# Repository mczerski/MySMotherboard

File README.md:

# MySMotherboard
## Motherboard for MySensors nodes

This is a motherboard for creating MySensors nodes based on the atmega328p MCU. It is meant to be combined with a MySX daughter board to create fully functional MySensors node. It is primarly for battery powered nodes but can be also used as a gateway or ac powered node (ac power supply is not part of this project). It features multiple powering options and supports RS485 or RFM69 RF communication options. The size of the board is just a little bigger than a cr123a battery holder.

## Features:

1. atmega328p MCU
2. Multiple power source options:
  * CR123A battery or 16340 rechargable li-ion battery
  * CR2032 battery
  * JST-PH2 connector for rechargable li-ion battery
  * 24V on the 2.54mm screw terminal
  * VRAW from MySX connector
3. Multiple voltage regulator options:
  * MCP1640C boost converter with bypass option
  * TPS782 LDO linear regulator
  * AP63205WU buck converter
  * no voltage regulation - direct voltage from battery
4. Input voltage reverse polarity protection
5. Overvoltage protection for RS485 data lines
6. Battery voltage divider to monitor battery voltage
7. ATSHA204A supported
8. AT25DF512C flash suppoerted
9. RFM69 RF SMD module
10. RF module interrupt D2 pin can be disconnected if not used
11. SP3485 for RS485 communication
12. reset button
13. user button
14. user led
15. external oscillator for atmega

## HOW TO

### Minimum required parts to solder are:

1. MCU related parts:
C5, C6, C7, C10, IC5, R7
2. Radio module related parts:
C1, R1, RFM69W, antenna to ANT pad and R12 (R12 is just a 0Ohm jumper required to connect RFM69 interrupt with D2 pin)
3. RS485 interface related parts:
U8
3. MySX connector:
X2

This is bare minimum that is required to start with this board. In this configuration the board can be powered from the MySX connector VCC pin with voltage between 1.9V - 3.6V.

### Optional parts to solder are:

1. MCU related parts:
 * for user led - R8, D1
 * for reset button - RST
 * for user button connected to D2 pin - BTN
 * for I2C pull-up resistors - R9, R10
 * for external oscillator - C8, C9, Q2
2. External flash related parts:
R2, IC2
WARNING: flash chips consumes a lot of uA of current so it is not suited for battery powered nodes.
3. ATSHA204A related parts:
IC3
ATSHA204A requires at least 2.0V power supply
4. RS485 related parst (overvoltage protection on data pins):
F1, F2, D2, D3

### Powering options

The powering option is choosed in two steps. First is to select the voltage source, and second is to choose the voltage conversion type. Between the voltage source and the voltage converter ther is the reverse polarity protection mosfet Q1 which is required for all options and voltage divider for battery voltage monitoring which is not required.

Voltage source options are:
1. CR123A battery or 16340 rechargable li-ion battery. To select this option just solder CR123A battery holder.
2. CR2032 battery. To chosse this option just solder CR2032 battery holder.
3. JST-PH2 connector. To choose this option just solder the X1 connector.
4. 24V input on 2.54mm screw terminal
5. VRAW from MySX connector. To choose this option the J2 jumper must be shorted.

Reverse polarity battery protection:
Q1

Voltage divider for battery voltage monitoring:
R5, R6, C4

Voltage convertion options are:
1. MCP1640C boost converter
R3, R4, R11, C2, C3, L1, IC4, J1 jumper should connect VBOOST with VCC.
The MCP1640C boost converter can be put into bypass mode so it just passes the input voltage. It is controller by the A2 pin and the bypass mode is the default. The purpose of this functionality is to be able to run the MCU directly from the battery and to boost the voltage only for the moment required to make measurements with sensors that require higher voltages.
2. TPS782 LDO linear regulator
C13, C14, IC1. J1 jumper should connect VREG with VCC. The C12 should be replaced by the 0Ohm resistor. The C12 capacitor was designed for the APE8865 LDo which consumes much more current that TPS782.
3. AP63205WU buck converter
C1, C6, C11, U7, Q2 (for high voltage reverse polarity protection)
4. No voltage regulation
There is actually no direct way to shoose this option, but it can be done by shorting pins number 5 and 6 of the IC4 and J1 jumper should connect VBOOST with VCC.

### Powering examples.

1. Very low power temperature and humidity sensor based on the BME280 sensor.
This node uses the "No voltage conversion" option because the BME280 sensor can work with voltages as low as 1.2V. So the node may be powered just by 3V coin-cell battery. This type of node uses just CR2032 battery holder.

2. Very low power node with DS18B20 temperature sensors that require minimum 3V power supply.
This type of node uses MCP1640C boost converter to boost battery voltage for the measurement period. Use CR2032 battery holder and MCP1640C boost converter option. In the software controll properly the A2 pin to turn on/off boost conversion.

3. Motion sensor node.
Motion sensor such as AS312 consumes quite a lot of power and needs voltage between 2.7V and 3.3V. Powering it directly with 3V battery is not good, so we could use the boost converter. But boost converter makes to much noise for AS312 to work properly. The AS312 works the best with 3V LDO, so the power source should have higher voltage. The best options is to use 3.7V 16340 rechargable li-ion battery which fits into CR123A battery holder. Use TPS782 LDO option to power the MCU and RF module and short the J2 jumper to power the VRAW pin directly with 3.7V battery. Then the motion sensor daugher board should power the AS312 sensor with another LDO from the VRAW pin.

4. RS485 node.
RS485 node uses 24V input on the 2.54mm screw terminal which delivers power and RS485 communication to the board. It also utilises high voltage reverse polarity protection and overvoltage protection for data pins so any wiring mistakes will not cause damage to the board. Onboard AP63205WU buck converter provides 5V input voltage for the board which can be used directly or can be fed to the 3V LDO regulator. By soldering JP1 jumper 5V power can be connected to VRAW on the MySX connector.

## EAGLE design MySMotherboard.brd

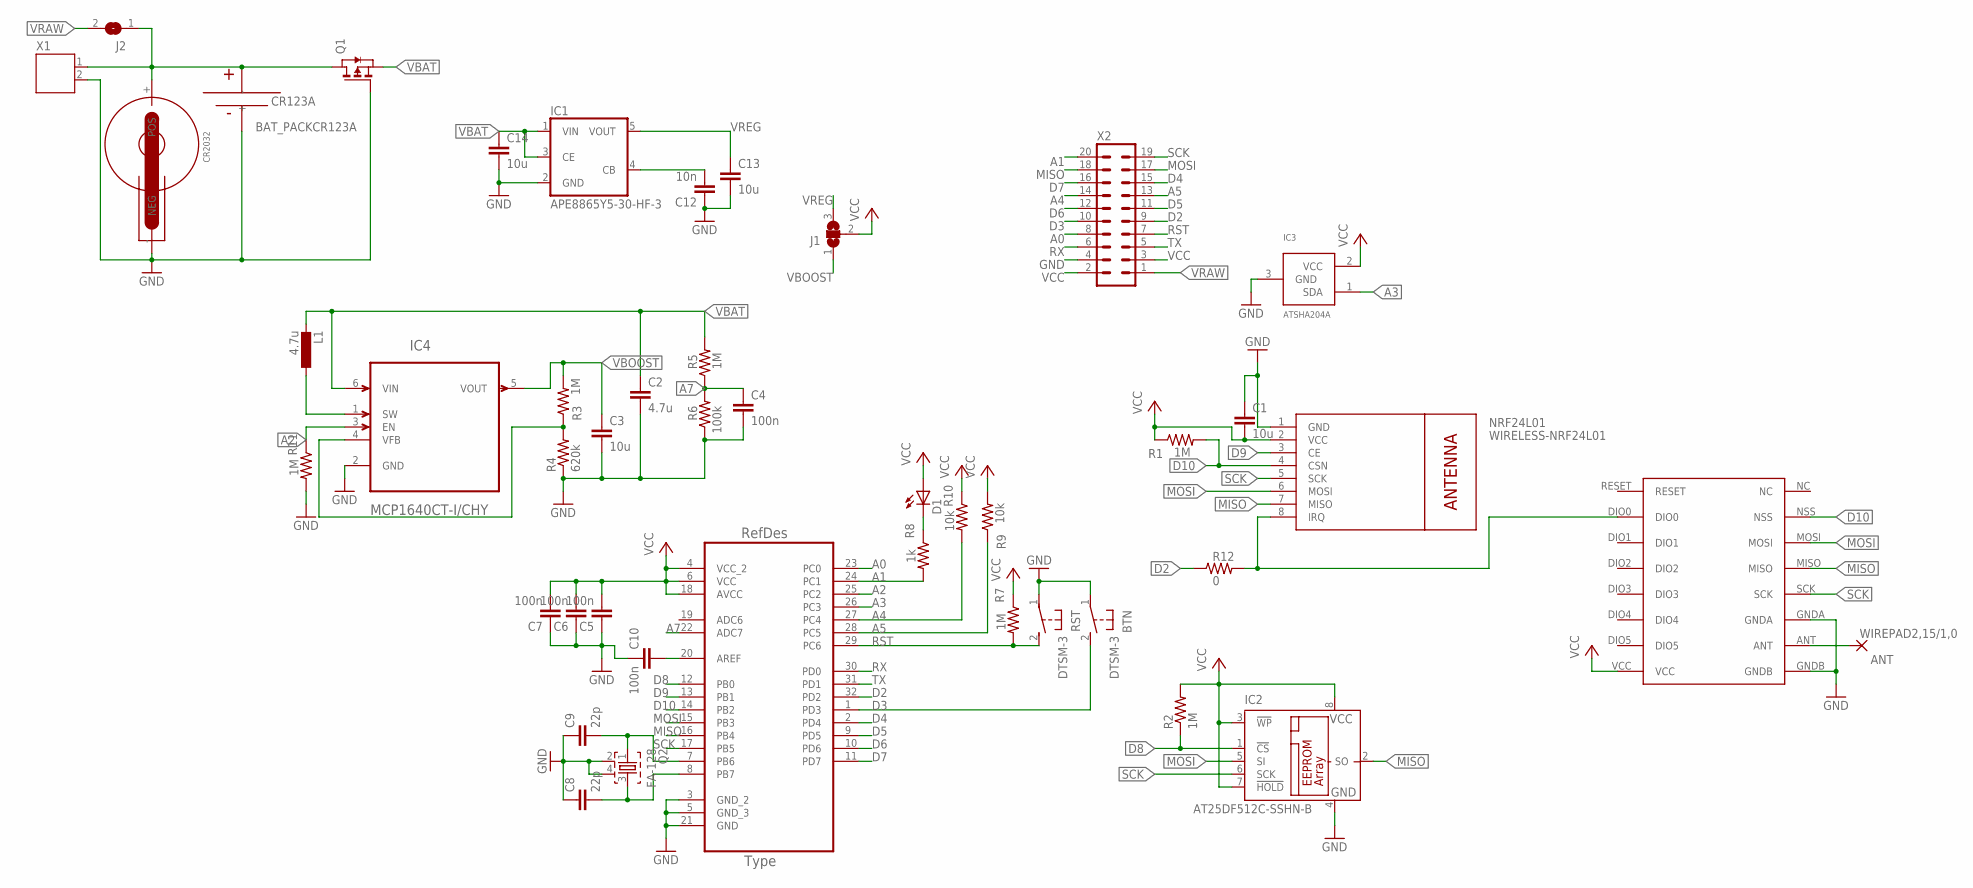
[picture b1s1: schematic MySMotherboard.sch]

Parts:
ANT: WIREPAD2,15/1,0; 2,15/1,0
BTN: DTSM-3
C1, C3, C13, C14: 10u; C0603K
C2: 4.7u; C0603K
C4, C5, C6, C7, C10: 100n; C0402
C8, C9: 22p; 0402-CAP
C12: 10n; C0402
CR123A: BAT_PACKCR123A; BH123A
CR2032: WA-BCPH_SMT_79527141; 79527141
D1: LEDCHIP-LED0805; CHIP-LED0805
IC1: APE8865Y5-30-HF-3; SOT25
IC2: AT25DF512C-SSHN-B; SO-08
IC3: ATSHA204A; SOT23
IC4: MCP1640CT-I/CHY; SOT95P270X145-6N
IC5: ATMEGA328P-AU; QFP80P900X900X120-32N
J1: SJ2W; SJ_2
J2: SJ
L1: 4.7u; L3225P
NRF24L01: WIRELESS-NRF24L01
Q1: PMOSSOT23; SOT-23
Q2: FA-128
R1, R2, R3, R7, R11: 1M; R0603
R4: 620k; R0603
R5: 1M; 0603-RES
R6: 100k; 0603-RES
R8: 1k; R0603
R9, R10: 10k; R0603
R12: 0; 0603-RES
RFM69W: RFM69HW; RFM
RST: DTSM-3
X1: JST-PH2
X2: MA10-2

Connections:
A0: IC5.23 (PC0), X2.8
A1: IC5.24 (PC1), R8.2, X2.20
A2: IC4.3 (EN), IC5.25 (PC2), R11.1
A3: IC3.1 (SDA), IC5.26 (PC3)
A4: IC5.27 (PC4), R10.2, X2.14
A5: IC5.28 (PC5), R9.1, X2.13
A7: C4.1, IC5.22 (ADC7), R5.1, R6.2
D2: IC5.32 (PD2), R12.1, X2.9
D3: BTN.2, IC5.1 (PD3), X2.10
D4: IC5.2 (PD4), X2.15
D5: IC5.9 (PD5), X2.11
D6: IC5.10 (PD6), X2.12
D7: IC5.11 (PD7), X2.16
D8: IC2.1 (!CS), IC5.12 (PB0), R2.1
D9: IC5.13 (PB1), NRF24L01.3 (CE)
D10: IC5.14 (PB2), NRF24L01.4 (CSN), R1.2, RFM69W.NSS
GND: BTN.1, C1.1, C2.2, C3.2, C4.2, C5.1, C6.1, C7.1, C8.1, C9.1, C10.2, C12.1, C13.2, C14.2, CR123A.-, CR2032.- (NEG), IC1.2 (GND), IC2.4 (GND), IC3.3 (GND), IC4.2 (GND), IC5.3 (GND_2), IC5.5 (GND_3), IC5.21 (GND), NRF24L01.1 (GND), Q1.3 (G), Q2.2, Q2.4, R4.1, R6.1, R11.2, RFM69W.GNDA, RFM69W.GNDB, RST.1, X1.2, X2.4
MISO: IC2.2 (SO), IC5.16 (PB4), NRF24L01.7 (MISO), RFM69W.MISO, X2.18
MOSI: IC2.5 (SI), IC5.15 (PB3), NRF24L01.6 (MOSI), RFM69W.MOSI, X2.17
unnamed: IC4.4 (VFB), R3.1, R4.2
unnamed: C8.2, IC5.8 (PB7), Q2.3
unnamed: C10.1, IC5.20 (AREF)
unnamed: IC4.1 (SW), L1.1
unnamed: ANT.1, RFM69W.ANT
unnamed: C9.2, IC5.7 (PB6), Q2.1
unnamed: CR123A.+, CR2032.+ (POS), J2.1, Q1.1 (D), X1.1
unnamed: C12.2, IC1.4 (CB)
unnamed: NRF24L01.8 (IRQ), R12.2, RFM69W.DIO0
unnamed: D1.C, R8.1
RST: IC5.29 (PC6), R7.2, RST.2, X2.7
RX: IC5.30 (PD0), X2.6
SCK: IC2.6 (SCK), IC5.17 (PB5), NRF24L01.5 (SCK), RFM69W.SCK, X2.19
TX: IC5.31 (PD1), X2.5
VBAT: C2.1, C14.1, IC1.1 (VIN), IC1.3 (CE), IC4.6 (VIN), L1.2, Q1.2 (S), R5.2
VBOOST: C3.1, IC4.5 (VOUT), J1.1, R3.2
VCC: C1.2, C5.2, C6.2, C7.2, D1.A, IC2.3 (!WP), IC2.7 (!HOLD), IC2.8 (VCC), IC3.2 (VCC), IC5.4 (VCC_2), IC5.6 (VCC), IC5.18 (AVCC), J1.2, NRF24L01.2 (VCC), R1.1, R2.2, R7.1, R9.2, R10.1, RFM69W.VCC, X2.2, X2.3
VRAW: J2.2, X2.1
VREG: C13.1, IC1.5 (VOUT), J1.3

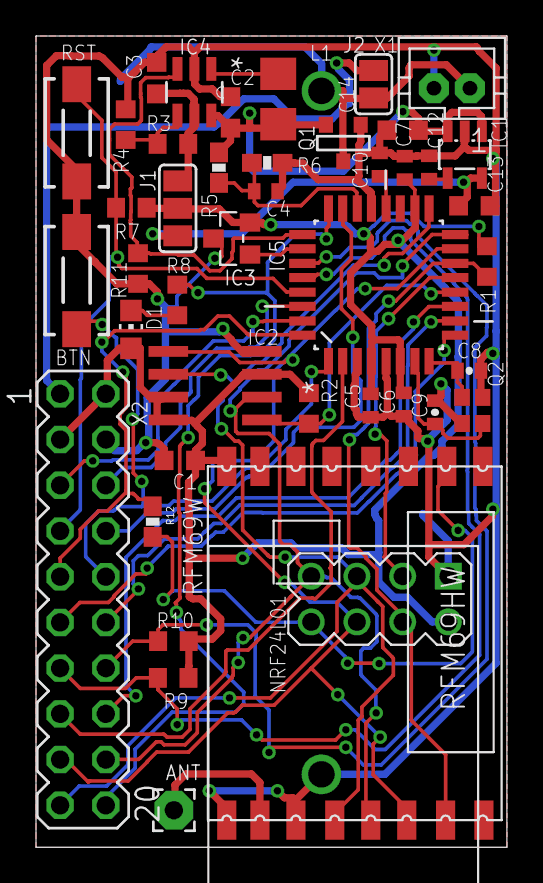
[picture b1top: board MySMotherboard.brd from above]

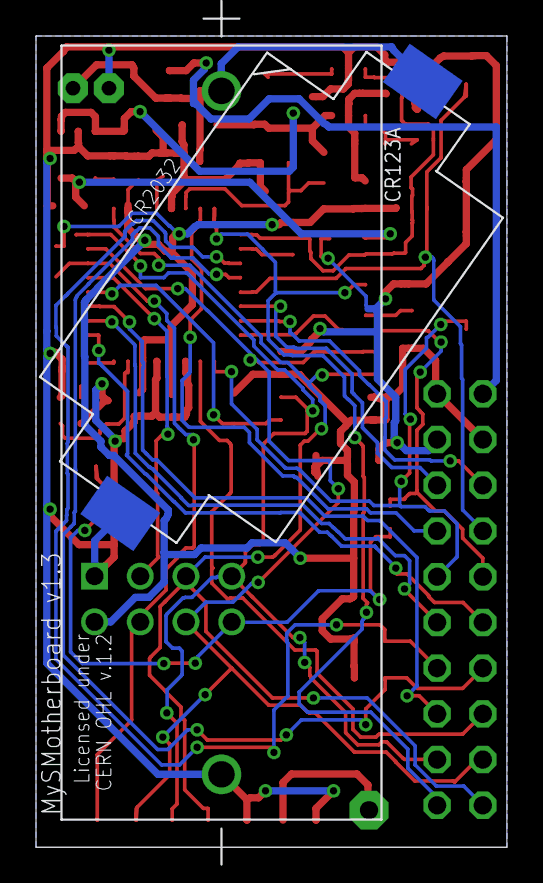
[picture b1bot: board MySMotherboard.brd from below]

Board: 2 copper layers, 26.2 x 45.1 mm, 45 parts (2 on the bottom side), 38 nets.

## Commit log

2017-10-14 initial commit - raw version, just schematic and pcb layout
2017-12-07 1. fix wrong boost converter footprint 2. connect led to A1 pin instead of A2 (which was used by the boost converter enable 3. change crystal footrint but not change the pcb
2017-12-07 1. rearrange nfr24l01 connector and atmega328p chip
2018-02-08 connect radio module irq with d2
2018-05-15 use p-mosfet for reverse polarity
2018-05-17 add RFM69
2018-06-10 remove eagle.epf from repo
2018-06-10 add 0Ohm resistor for radio module interrupt + connect button to D3
2018-06-10 move ldo to top layer
2018-06-10 rotate cr2032 battery pack to about 55 degrees
2018-07-22 rename files
2018-07-22 add pictures
2018-07-22 add documentation files
2018-07-22 add new foto
2018-07-23 add license documentation
2018-07-23 update gerbers after adding license notice
2024-05-20 convert to KiCad
2024-05-22 refactor schematic to use native KiCad symbols and footprints
2024-05-25 replace NRF24L01 with RS485 inteface
2024-06-07 change bypass capacitor for buck dc/dc converter to 50V 0603
2024-06-07 add protection circuitry for RS485 IC AB lines
2024-06-07 add reverse polarity protection for 24V input
2024-06-08 update PCB with latest changes
2024-06-08 update README and schematic pdf export
2024-06-08 update gerber files
2024-06-08 change 22uF cap on buck converter output to 10uF
    10uF should be sufficient
2024-06-08 change bypass capacitor for buck converter from 0603 to 0402
2024-07-24 update parts documentation sources
2025-01-03 update to kicad 8
2025-10-19 add pull-up resistor for RFM69W NSS pin
2025-10-19 add option to connect RFM69W irq to pin 3
2025-10-19 update production files

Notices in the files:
MySMotherboard.brd:
Licensed under
CERN OHL v.1.2
parts and their libraries:
SparkFun-Passives: Licensing: Creative Commons ShareAlike 4.0 International - https://creativecommons.org/licenses/by-sa/4.0
diy-modules: Released under the Creative Commons Attribution 4.0 International License: http://creativecommons.org/licenses/by/4.0
